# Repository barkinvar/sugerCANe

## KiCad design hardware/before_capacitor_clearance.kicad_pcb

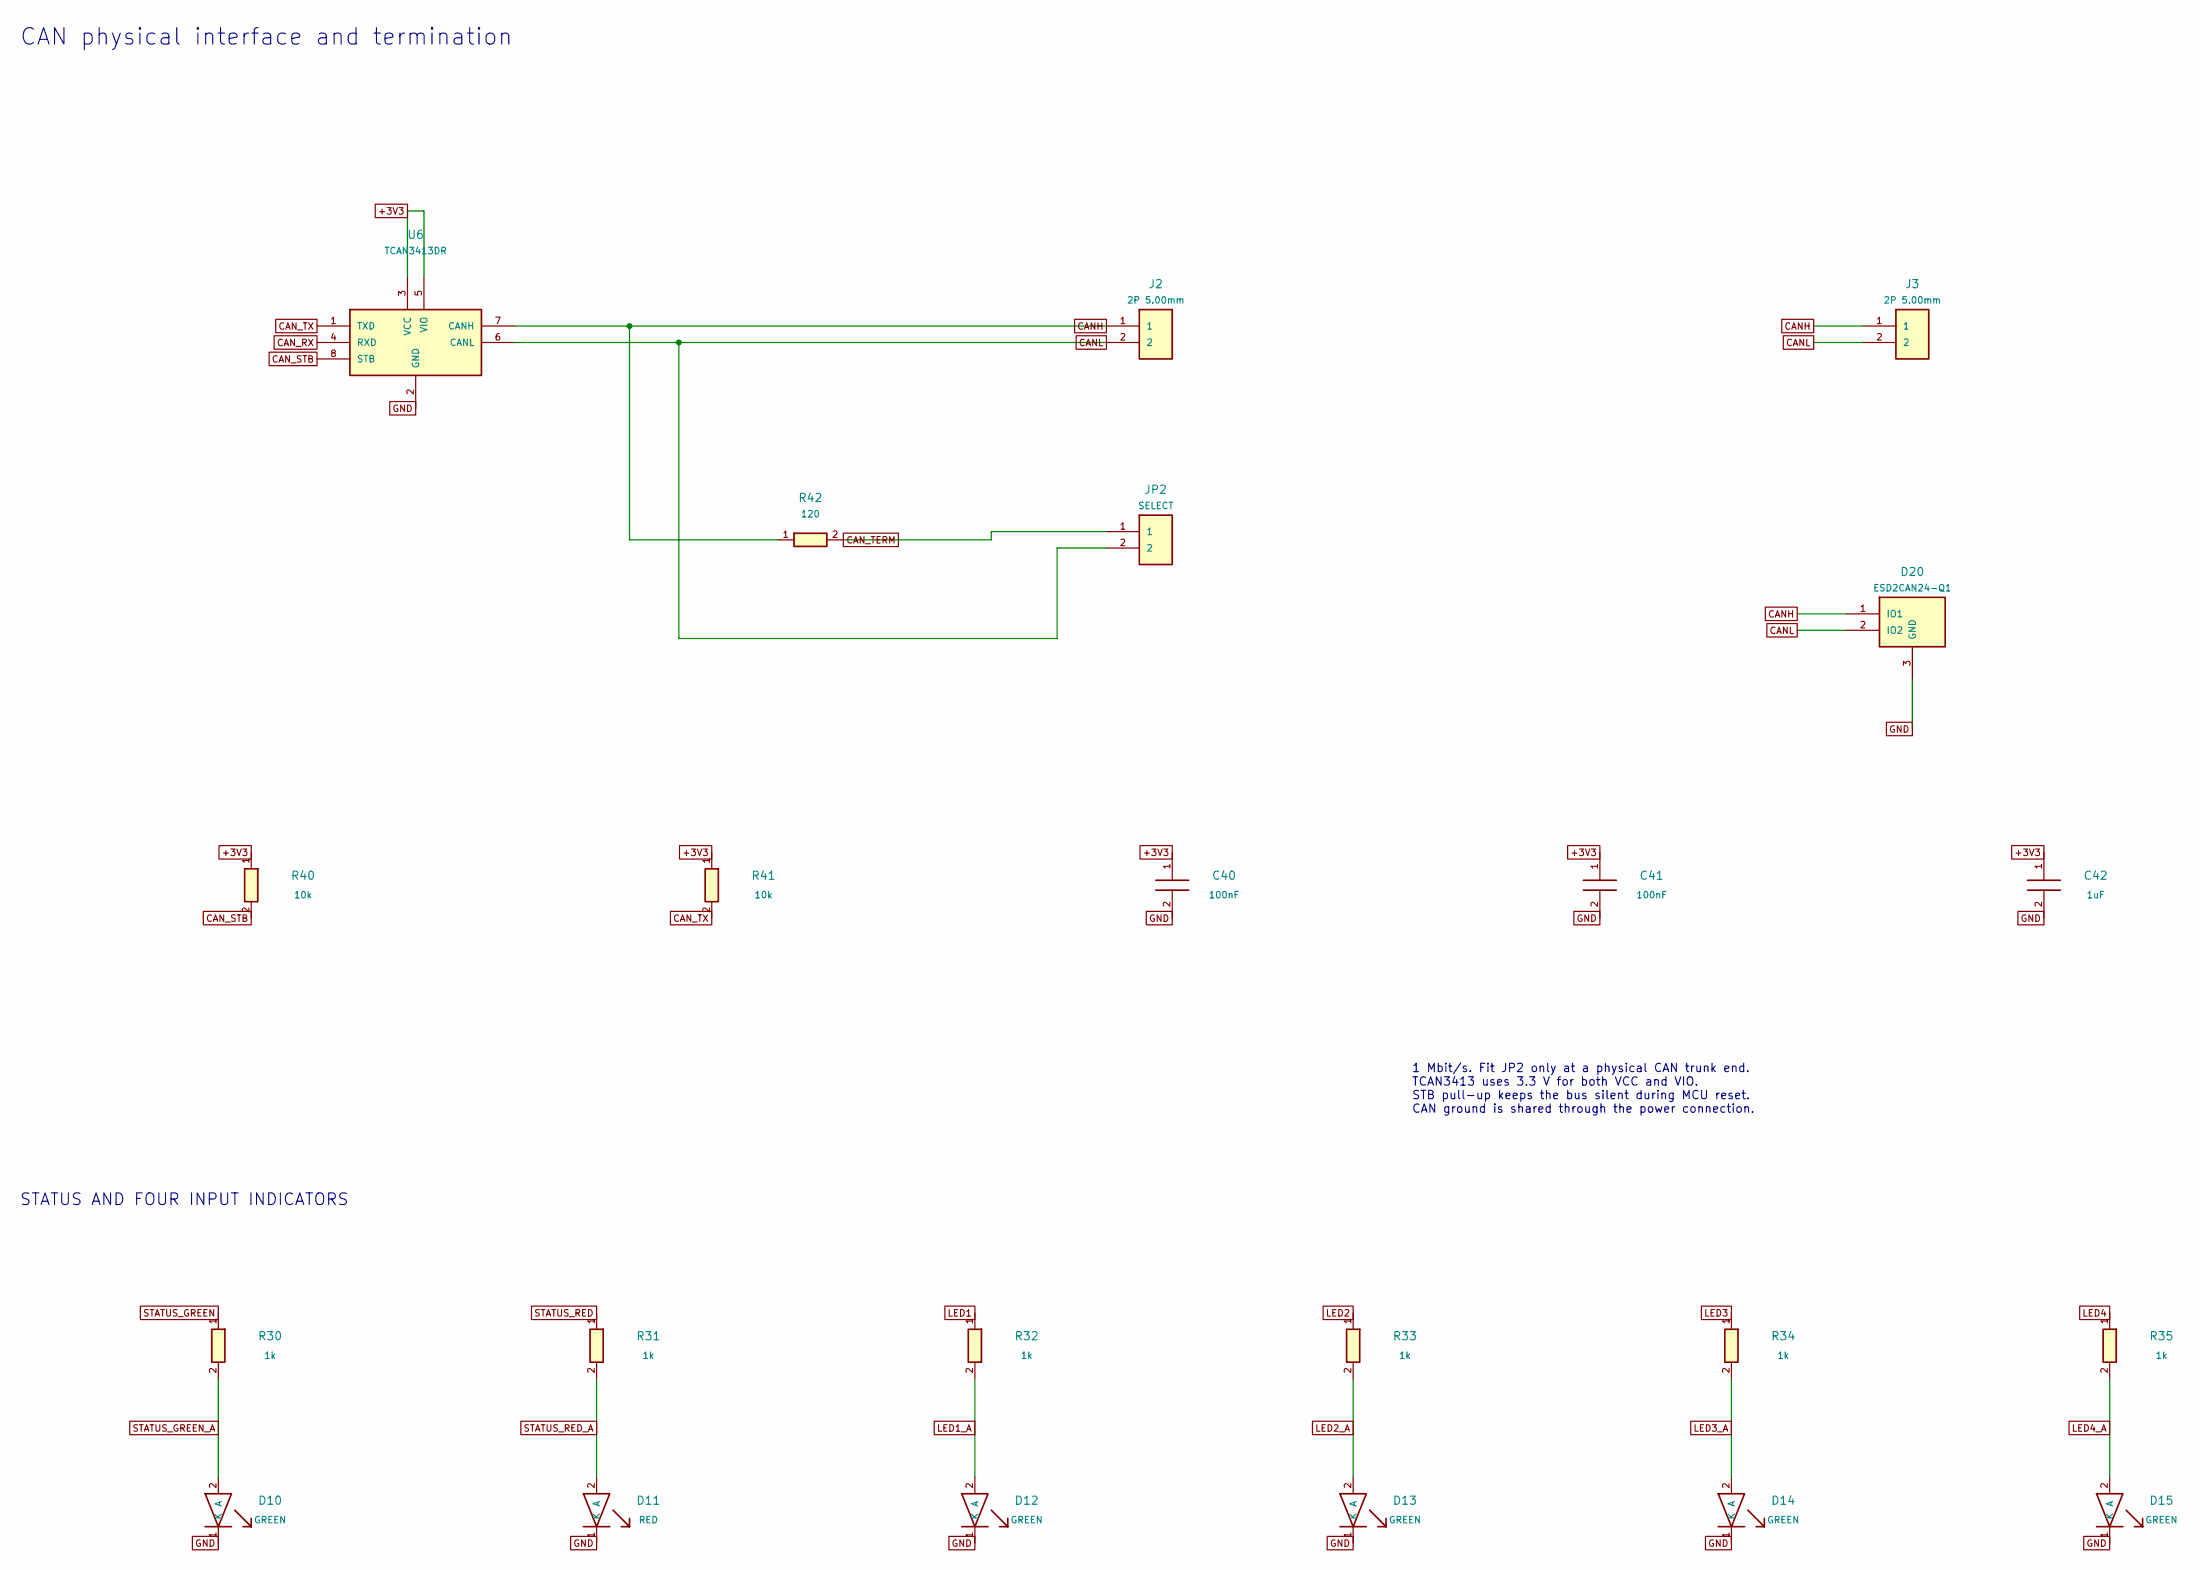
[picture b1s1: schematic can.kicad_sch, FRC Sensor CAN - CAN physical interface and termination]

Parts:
C40, C41: 100nF; C_0805_2012Metric; MPN CC0805KRX7R9BB104
C42: 1uF; C_0805_2012Metric; MPN CC0805KKX7R9BB105
D10, D12, D13, D14, D15: GREEN; LED_0805_2012Metric; MPN LTST-C170KGKT
D11: RED; LED_0805_2012Metric; MPN LTST-C170KRKT
D20: ESD2CAN24-Q1; SOT-23; MPN ESD2CAN24DBZRQ1
J2, J3: 2P 5.00mm; Wuerth_691137710002; MPN 691137710002
JP2: SELECT; PinHeader_1x02_P2.54mm_Vertical; MPN M20-9990245
R30, R31, R32, R33, R34, R35: 1k; R_0805_2012Metric; MPN RC0805FR-071KL
R40, R41: 10k; R_0805_2012Metric; MPN RC0805FR-0710KL
R42: 120; R_1206_3216Metric; MPN RC1206FR-07120RL
U6: TCAN3413DR; SOIC-8_3.9x4.9mm_P1.27mm; MPN TCAN3413DR

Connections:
+3V3: C40.1, C41.1, C42.1, R40.1, R41.1, U6.3 (VCC), U6.5 (VIO); also elsewhere on the board
CANH: D20.1 (IO1), J2.1, J3.1, R42.1, U6.7 (CANH)
CANL: D20.2 (IO2), J2.2, J3.2, JP2.2, U6.6 (CANL)
CAN_RX: U6.4 (RXD); also elsewhere on the board
CAN_STB: R40.2, U6.8 (STB); also elsewhere on the board
CAN_TERM: JP2.1, R42.2
CAN_TX: R41.2, U6.1 (TXD); also elsewhere on the board
GND: C40.2, C41.2, C42.2, D10.1 (K), D11.1 (K), D12.1 (K), D13.1 (K), D14.1 (K), D15.1 (K), D20.3 (GND), U6.2 (GND); also elsewhere on the board
LED1: R32.1; also elsewhere on the board
LED1_A: D12.2 (A), R32.2
LED2: R33.1; also elsewhere on the board
LED2_A: D13.2 (A), R33.2
LED3: R34.1; also elsewhere on the board
LED3_A: D14.2 (A), R34.2
LED4: R35.1; also elsewhere on the board
LED4_A: D15.2 (A), R35.2
STATUS_GREEN: R30.1; also elsewhere on the board
STATUS_GREEN_A: D10.2 (A), R30.2
STATUS_RED: R31.1; also elsewhere on the board
STATUS_RED_A: D11.2 (A), R31.2

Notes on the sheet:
CAN physical interface and termination
1 Mbit/s. Fit JP2 only at a physical CAN trunk end. TCAN3413 uses 3.3 V for both VCC and VIO. STB pull-up keeps the bus silent during MCU reset. CAN ground is shared through the power connection.
STATUS AND FOUR INPUT INDICATORS

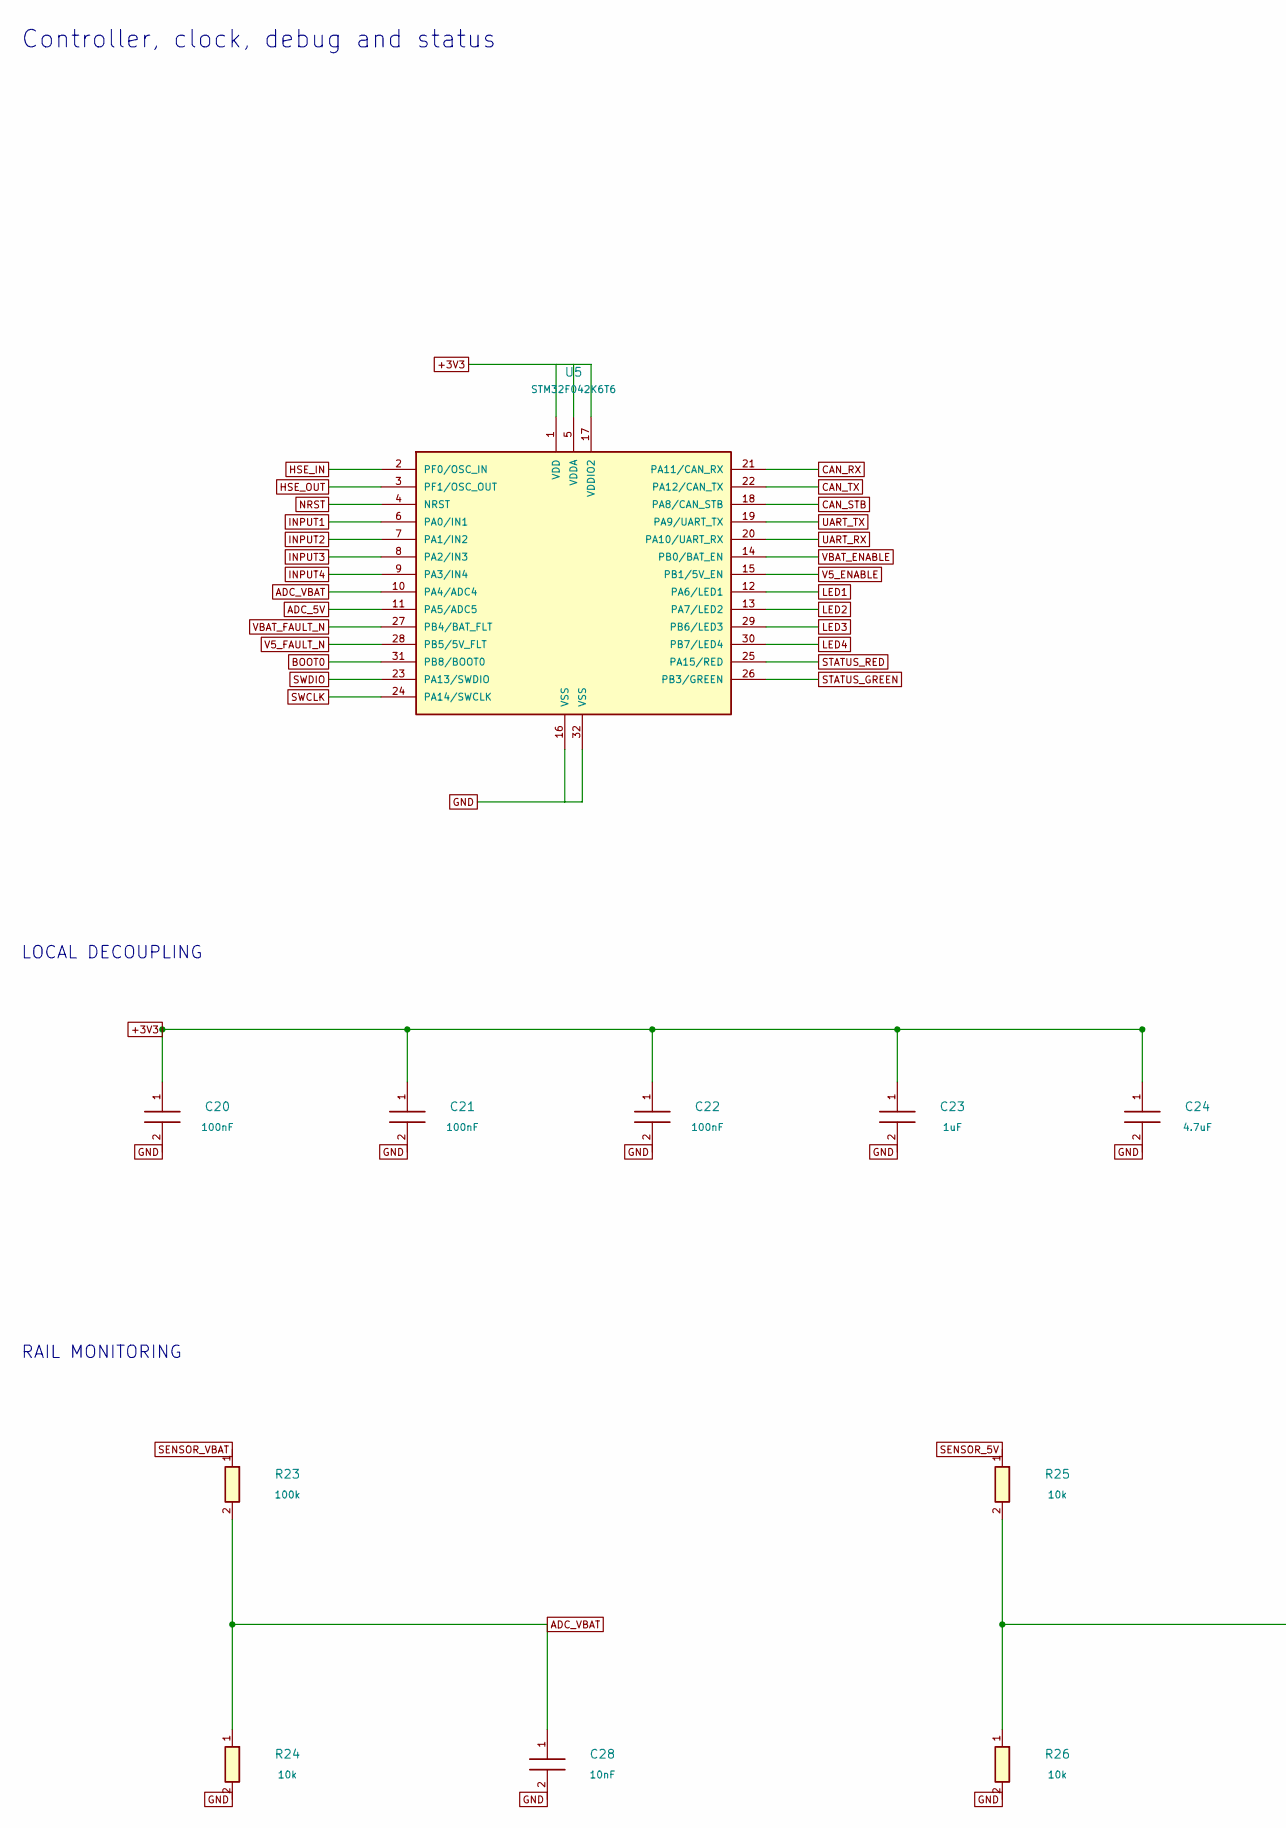
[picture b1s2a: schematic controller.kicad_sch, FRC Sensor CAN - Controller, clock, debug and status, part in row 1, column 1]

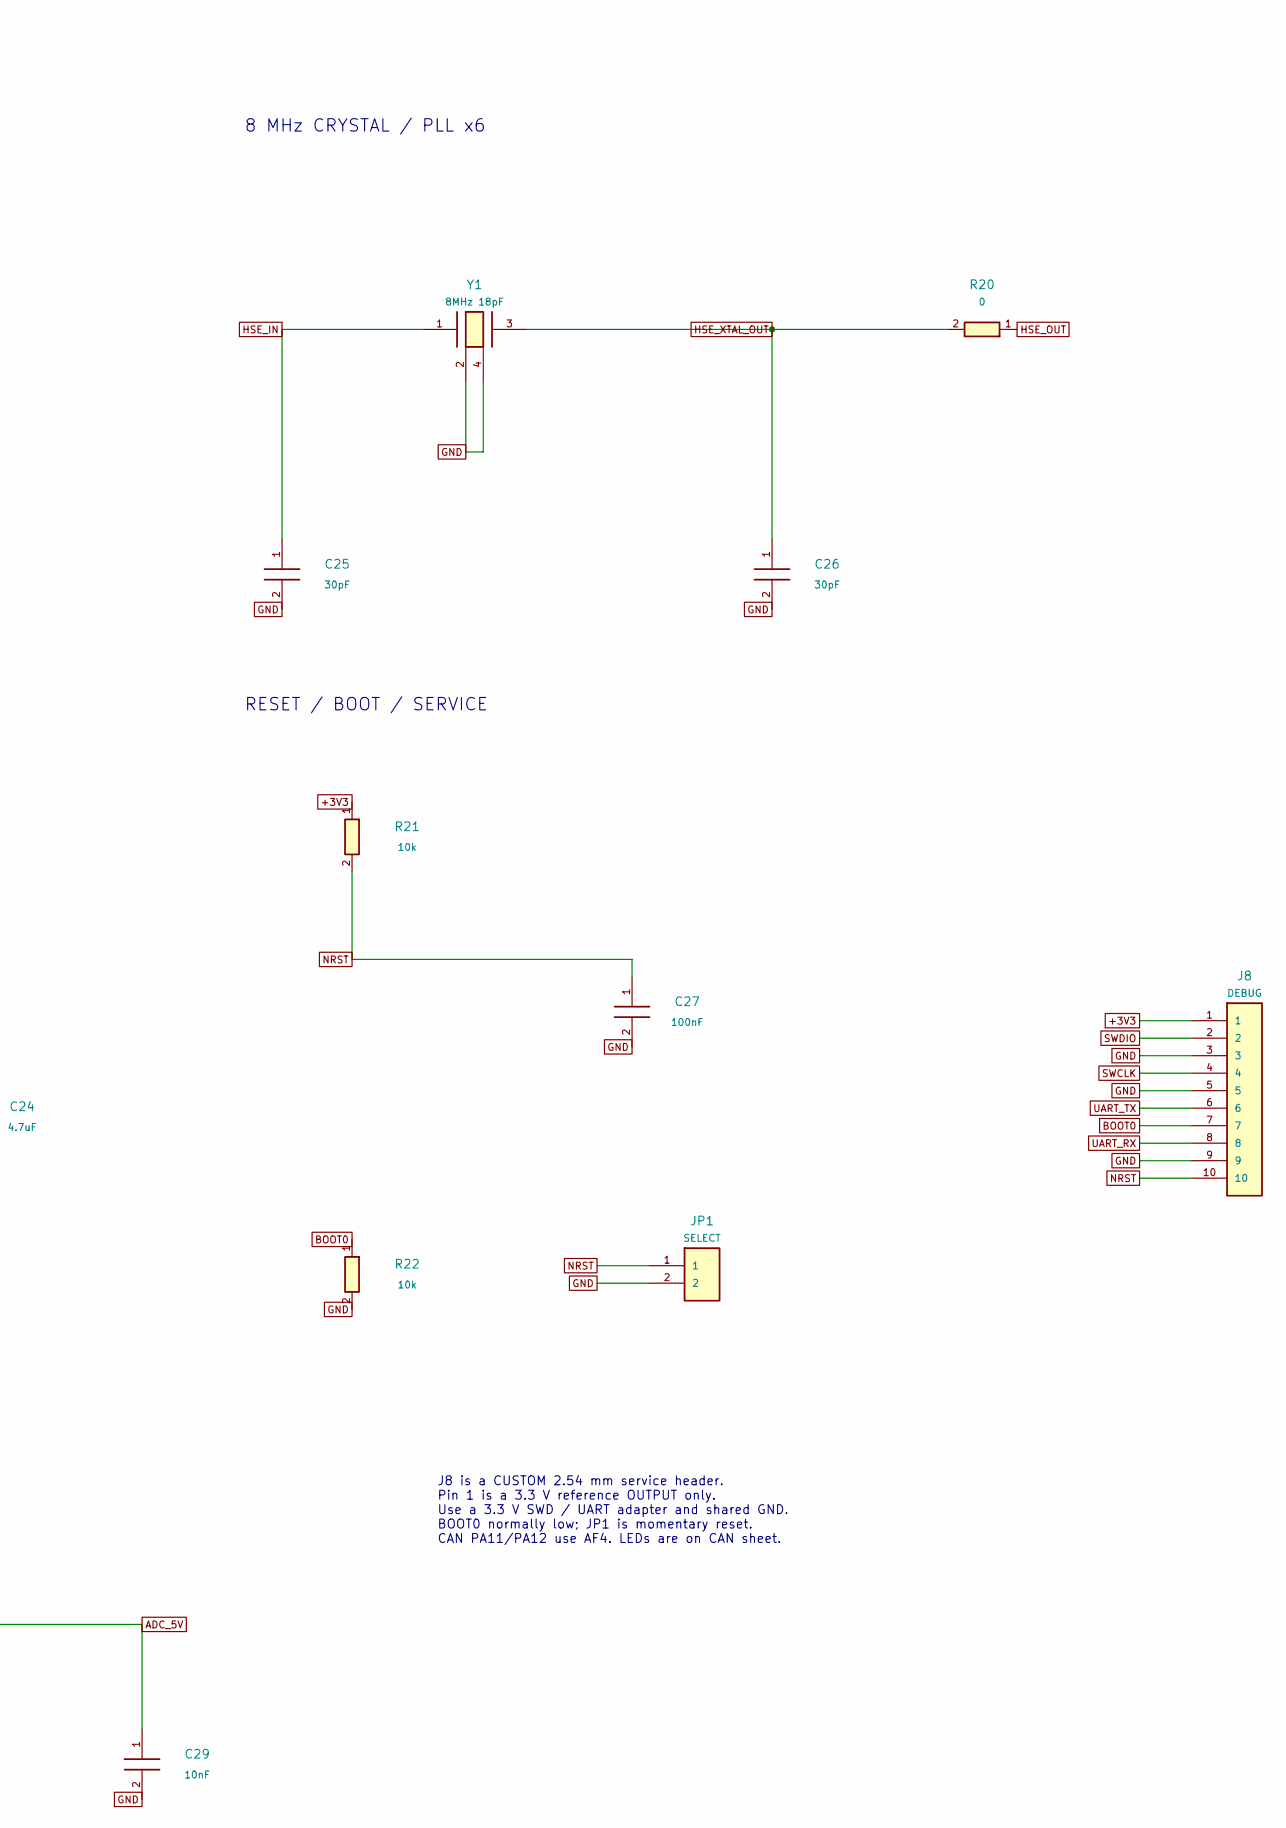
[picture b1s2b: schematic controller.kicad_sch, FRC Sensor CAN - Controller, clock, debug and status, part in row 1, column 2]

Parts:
C20, C21, C22, C27: 100nF; C_0805_2012Metric; MPN CC0805KRX7R9BB104
C23: 1uF; C_0805_2012Metric; MPN CC0805KKX7R9BB105
C24: 4.7uF; C_0805_2012Metric; MPN TMK212AB7475KG-T
C25, C26: 30pF; C_0805_2012Metric; MPN C0805C300J5GACTU
C28, C29: 10nF; C_0805_2012Metric; MPN CC0805KRX7R9BB103
J8: DEBUG; PinHeader_2x05_P2.54mm_Vertical; MPN M20-9980545
JP1: SELECT; PinHeader_1x02_P2.54mm_Vertical; MPN M20-9990245
R20: 0; R_0805_2012Metric; MPN RC0805JR-070RL
R21, R22, R24, R25, R26: 10k; R_0805_2012Metric; MPN RC0805FR-0710KL
R23: 100k; R_0805_2012Metric; MPN RC0805FR-07100KL
U5: STM32F042K6T6; LQFP-32_7x7mm_P0.8mm; MPN STM32F042K6T6
Y1: 8MHz 18pF; Abracon_ABM3B_5.0x3.2mm; MPN ABM3B-8.000MHZ-B2-T

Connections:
+3V3: C20.1, C21.1, C22.1, C23.1, C24.1, J8.1, R21.1, U5.1 (VDD), U5.5 (VDDA), U5.17 (VDDIO2); also elsewhere on the board
ADC_5V: C29.1, R25.2, R26.1, U5.11 (PA5/ADC5)
ADC_VBAT: C28.1, R23.2, R24.1, U5.10 (PA4/ADC4)
BOOT0: J8.7, R22.1, U5.31 (PB8/BOOT0)
CAN_RX: U5.21 (PA11/CAN_RX); also elsewhere on the board
CAN_STB: U5.18 (PA8/CAN_STB); also elsewhere on the board
CAN_TX: U5.22 (PA12/CAN_TX); also elsewhere on the board
GND: C20.2, C21.2, C22.2, C23.2, C24.2, C25.2, C26.2, C27.2, C28.2, C29.2, J8.3, J8.5, J8.9, JP1.2, R22.2, R24.2, R26.2, U5.16 (VSS), U5.32 (VSS), Y1.2, Y1.4; also elsewhere on the board
HSE_IN: C25.1, U5.2 (PF0/OSC_IN), Y1.1
HSE_OUT: R20.1, U5.3 (PF1/OSC_OUT)
HSE_XTAL_OUT: C26.1, R20.2, Y1.3
INPUT1: U5.6 (PA0/IN1); also elsewhere on the board
INPUT2: U5.7 (PA1/IN2); also elsewhere on the board
INPUT3: U5.8 (PA2/IN3); also elsewhere on the board
INPUT4: U5.9 (PA3/IN4); also elsewhere on the board
LED1: U5.12 (PA6/LED1); also elsewhere on the board
LED2: U5.13 (PA7/LED2); also elsewhere on the board
LED3: U5.29 (PB6/LED3); also elsewhere on the board
LED4: U5.30 (PB7/LED4); also elsewhere on the board
NRST: C27.1, J8.10, JP1.1, R21.2, U5.4 (NRST)
SENSOR_5V: R25.1; also elsewhere on the board
SENSOR_VBAT: R23.1; also elsewhere on the board
STATUS_GREEN: U5.26 (PB3/GREEN); also elsewhere on the board
STATUS_RED: U5.25 (PA15/RED); also elsewhere on the board
SWCLK: J8.4, U5.24 (PA14/SWCLK)
SWDIO: J8.2, U5.23 (PA13/SWDIO)
UART_RX: J8.8, U5.20 (PA10/UART_RX)
UART_TX: J8.6, U5.19 (PA9/UART_TX)
V5_ENABLE: U5.15 (PB1/5V_EN); also elsewhere on the board
V5_FAULT_N: U5.28 (PB5/5V_FLT); also elsewhere on the board
VBAT_ENABLE: U5.14 (PB0/BAT_EN); also elsewhere on the board
VBAT_FAULT_N: U5.27 (PB4/BAT_FLT); also elsewhere on the board

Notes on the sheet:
Controller, clock, debug and status
8 MHz CRYSTAL / PLL x6
RESET / BOOT / SERVICE
LOCAL DECOUPLING
RAIL MONITORING
J8 is a CUSTOM 2.54 mm service header. Pin 1 is a 3.3 V reference OUTPUT only. Use a 3.3 V SWD / UART adapter and shared GND. BOOT0 normally low; JP1 is momentary reset. CAN PA11/PA12 use AF4. LEDs are on CAN sheet.

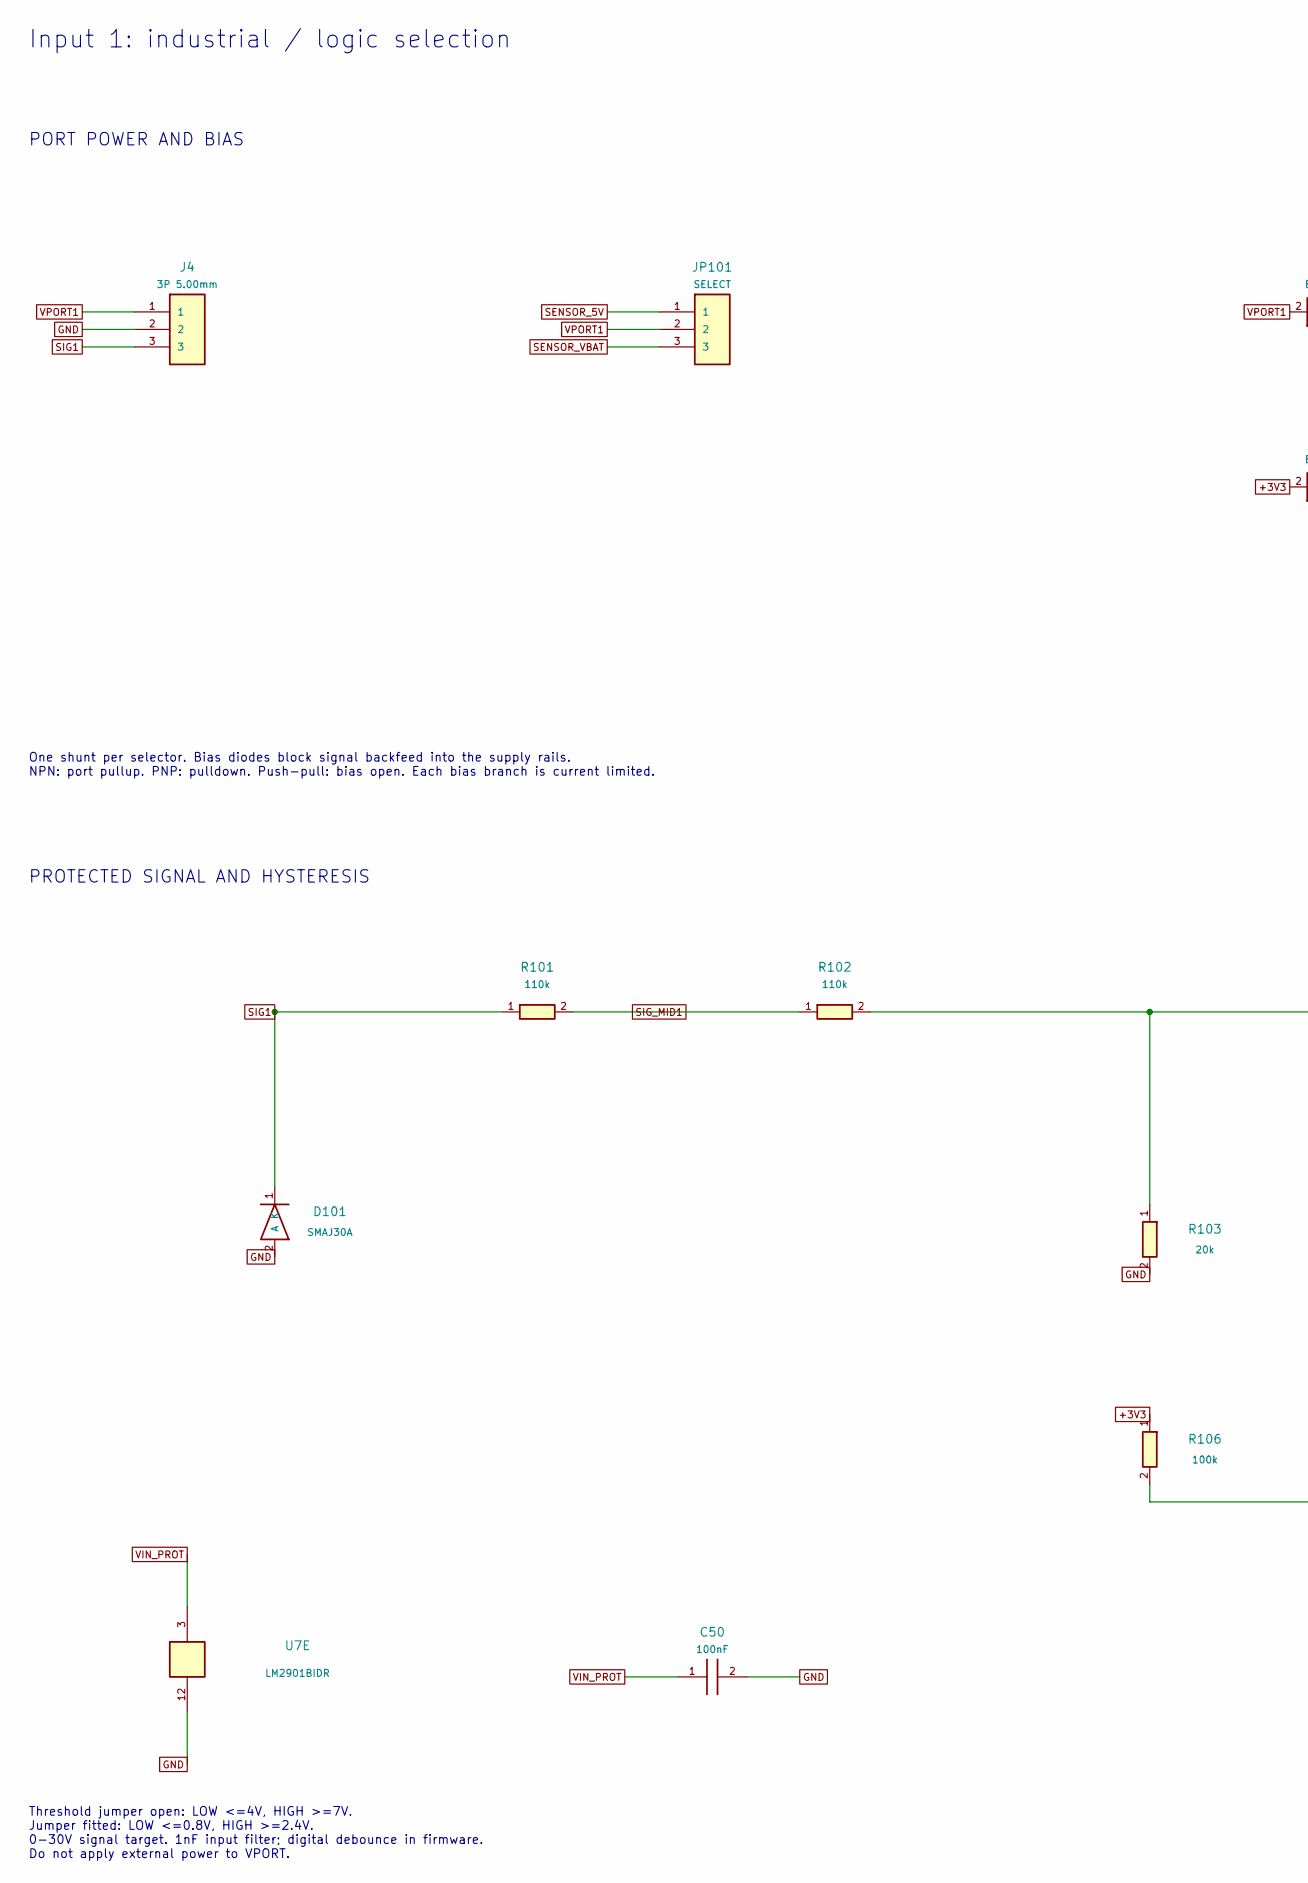
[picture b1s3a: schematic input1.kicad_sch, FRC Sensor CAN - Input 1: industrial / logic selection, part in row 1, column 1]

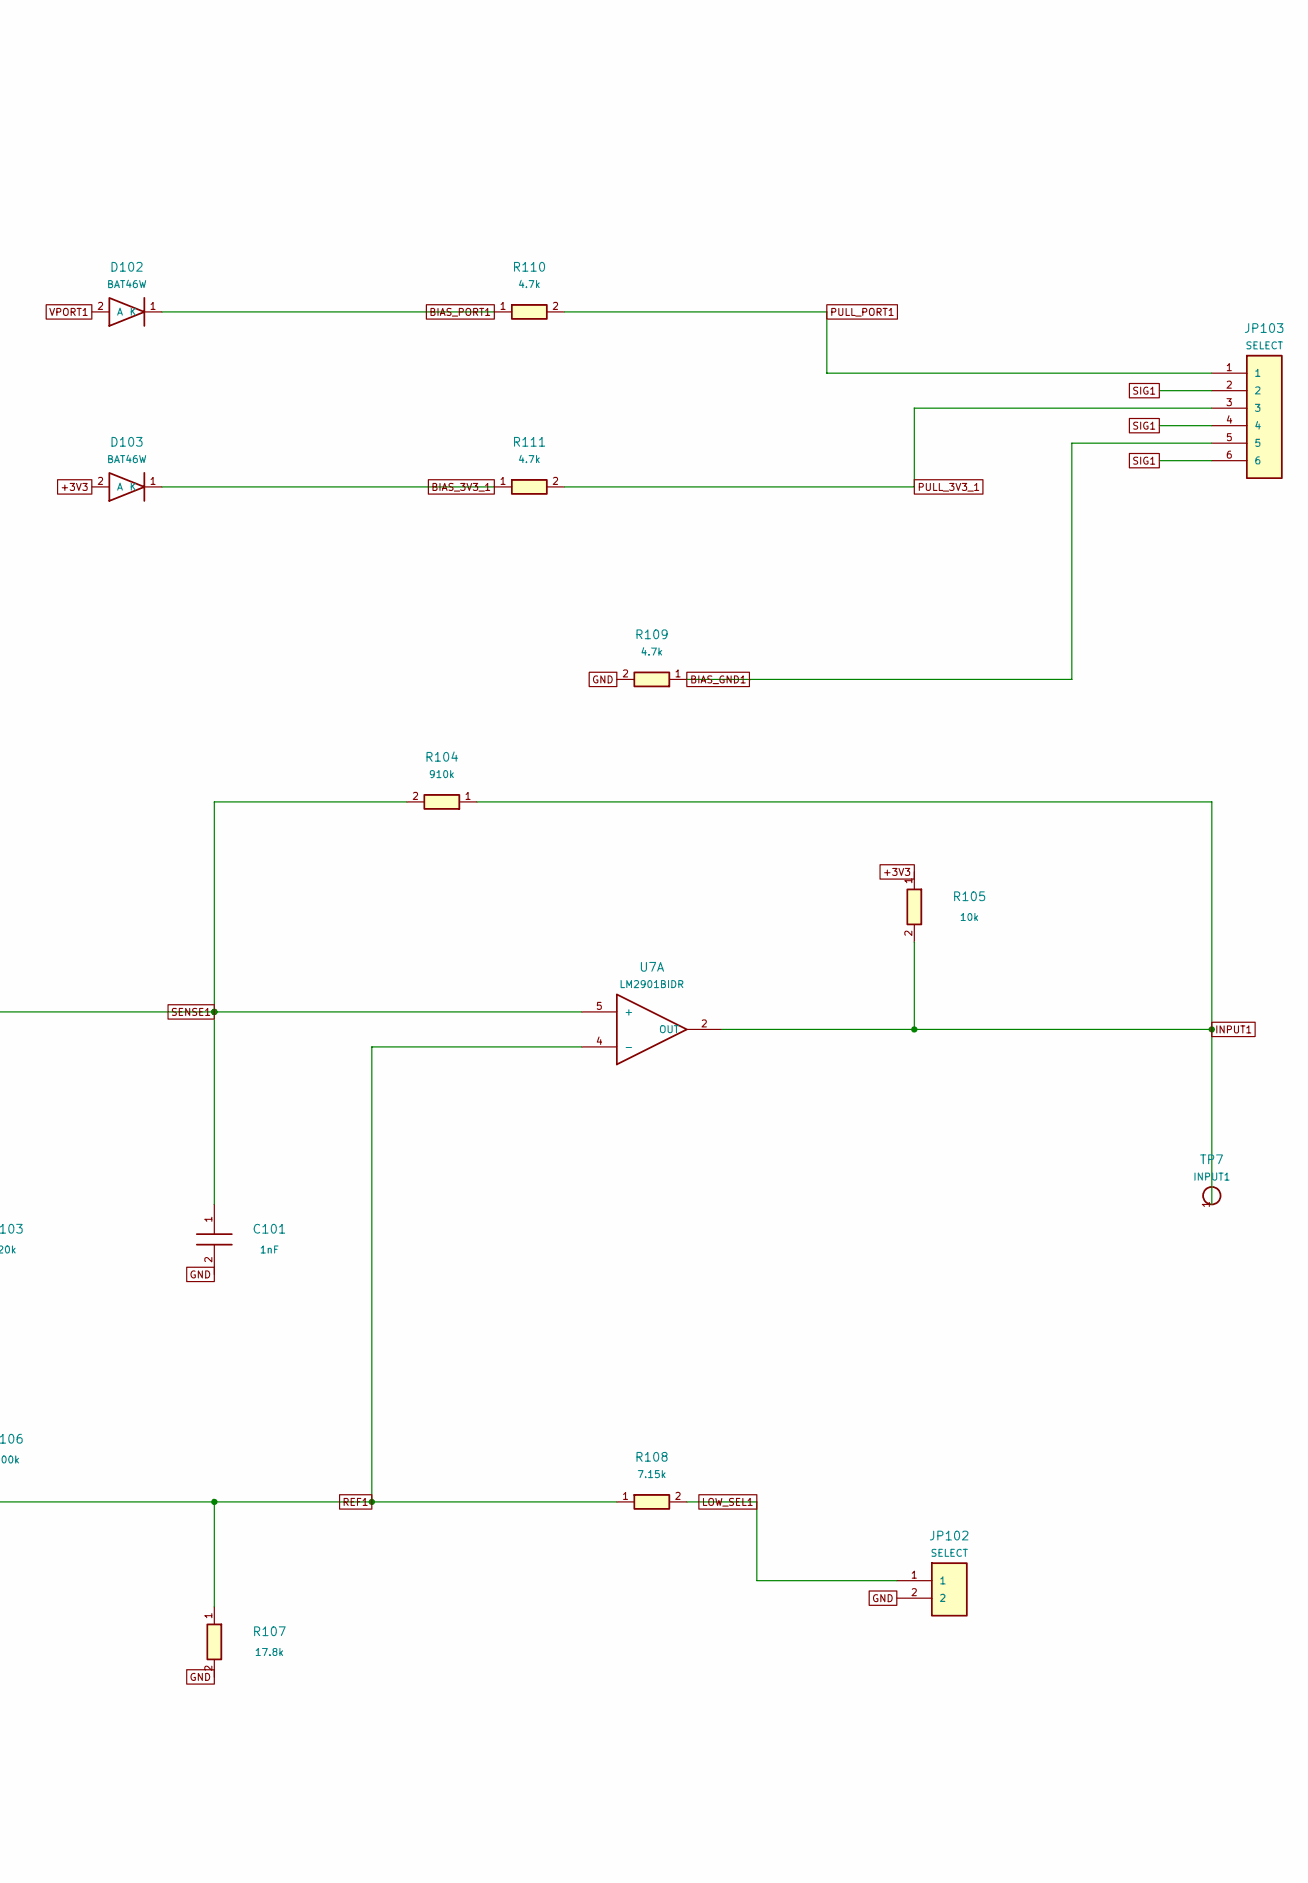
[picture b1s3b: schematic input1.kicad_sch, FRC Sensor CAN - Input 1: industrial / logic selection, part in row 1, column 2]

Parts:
C50: 100nF; C_0805_2012Metric; MPN CC0805KRX7R9BB104
C101: 1nF; C_0805_2012Metric; MPN CC0805JRNPO9BN102
D101: SMAJ30A; D_SMA; MPN SMAJ30A
D102, D103: BAT46W; D_SOD-123; MPN BAT46W-E3-18
J4: 3P 5.00mm; Wuerth_691137710003; MPN 691137710003
JP101: SELECT; PinHeader_1x03_P2.54mm_Vertical; MPN M20-9990345
JP102: SELECT; PinHeader_1x02_P2.54mm_Vertical; MPN M20-9990245
JP103: SELECT; PinHeader_2x03_P2.54mm_Vertical; MPN M20-9980345
R101, R102: 110k; R_0805_2012Metric; MPN RC0805FR-07110KL
R103: 20k; R_0805_2012Metric; MPN RC0805FR-0720KL
R104: 910k; R_0805_2012Metric; MPN RC0805FR-07910KL
R105: 10k; R_0805_2012Metric; MPN RC0805FR-0710KL
R106: 100k; R_0805_2012Metric; MPN RC0805FR-07100KL
R107: 17.8k; R_0805_2012Metric; MPN ERJ-6ENF1782V
R108: 7.15k; R_0805_2012Metric; MPN RC0805FR-077K15L
R109: 4.7k; R_2010_5025Metric; MPN RC2010FK-074K7L
R110, R111: 4.7k; R_0805_2012Metric; MPN RC0805FR-074K7L
TP7: INPUT1; TestPoint_Pad_D2.0mm
U7: LM2901BIDR; SOIC-14_3.9x8.7mm_P1.27mm; MPN LM2901BIDR

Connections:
+3V3: D103.2 (A), R105.1, R106.1; also elsewhere on the board
BIAS_3V3_1: D103.1 (K), R111.1
BIAS_GND1: JP103.5, R109.1
BIAS_PORT1: D102.1 (K), R110.1
GND: C50.2, C101.2, D101.2 (A), J4.2, JP102.2, R103.2, R107.2, R109.2, U7.12; also elsewhere on the board
INPUT1: R104.1, R105.2, TP7.1, U7.2 (OUT); also elsewhere on the board
LOW_SEL1: JP102.1, R108.2
PULL_3V3_1: JP103.3, R111.2
PULL_PORT1: JP103.1, R110.2
REF1: R106.2, R107.1, R108.1, U7.4 (-)
SENSE1: C101.1, R102.2, R103.1, R104.2, U7.5 (+)
SENSOR_5V: JP101.1; also elsewhere on the board
SENSOR_VBAT: JP101.3; also elsewhere on the board
SIG1: D101.1 (K), J4.3, JP103.2, JP103.4, JP103.6, R101.1
SIG_MID1: R101.2, R102.1
VIN_PROT: C50.1, U7.3; also elsewhere on the board
VPORT1: D102.2 (A), J4.1, JP101.2

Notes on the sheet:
Input 1: industrial / logic selection
PORT POWER AND BIAS
One shunt per selector. Bias diodes block signal backfeed into the supply rails. NPN: port pullup. PNP: pulldown. Push-pull: bias open. Each bias branch is current limited.
PROTECTED SIGNAL AND HYSTERESIS
Threshold jumper open: LOW <=4V, HIGH >=7V. Jumper fitted: LOW <=0.8V, HIGH >=2.4V. 0-30V signal target. 1nF input filter; digital debounce in firmware. Do not apply external power to VPORT.
